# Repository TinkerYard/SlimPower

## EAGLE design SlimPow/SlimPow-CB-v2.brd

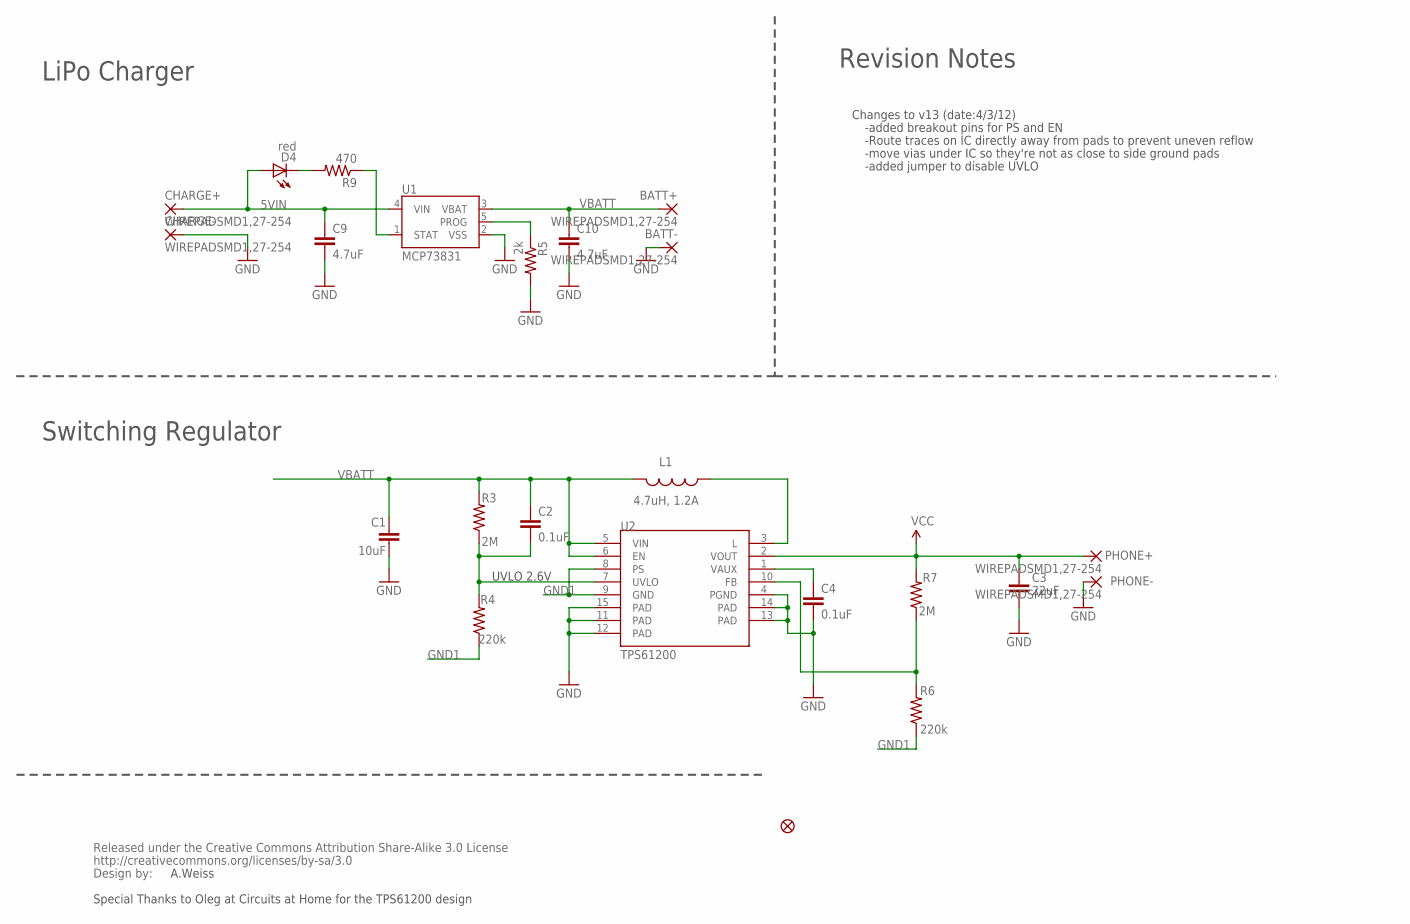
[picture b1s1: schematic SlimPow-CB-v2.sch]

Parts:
BATT+: WIREPADSMD1,27-254; SMD1,27-2,54
BATT-: WIREPADSMD1,27-254; SMD1,27-2,54
C1: 10uF; 1206
C2, C4: 0.1uF; 0402-CAP
C3: 22uF; 0805
C9, C10: 4.7uF; 0402-CAP
CHARGE+: WIREPADSMD1,27-254; SMD1,27-2,54
CHARGE-: WIREPADSMD1,27-254; SMD1,27-2,54
D4: red; LED-0603
JP15: FIDUCIALUFIDUCIAL; MICRO-FIDUCIAL
L1: 4.7uH, 1.2A; CDRH2D09
PHONE+: WIREPADSMD1,27-254; SMD1,27-2,54
PHONE-: WIREPADSMD1,27-254; SMD1,27-2,54
R3, R7: 2M; 0402-RES
R4, R6: 220k; 0402-RES
R5: 2k; 0402-RES
R9: 470; 0402-RES
U1: MCP73831; SOT23-5
U2: TPS61200; QFN-10_PAD
U$2: CREATIVE_COMMONS

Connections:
5VIN: C9.1, CHARGE+.1, D4.A, U1.4 (VIN)
FB: R6.2, R7.1, U2.10 (FB)
GND: BATT-.1, C1.2, C3.2, C4.2, C9.2, C10.2, CHARGE-.1, PHONE-.1, R5.2, U1.2 (VSS), U2.4 (PGND), U2.11 (PAD), U2.12 (PAD), U2.13 (PAD), U2.14 (PAD), U2.15 (PAD)
GND1: R4.1, R6.1, U2.8 (PS), U2.9 (GND)
unnamed: C4.1, U2.1 (VAUX)
unnamed: L1.P$1 (1), U2.3 (L)
unnamed: D4.C, R9.2
unnamed: R5.1, U1.5 (PROG)
unnamed: R9.1, U1.1 (STAT)
UVLO: C2.2, R3.1, R4.2, U2.7 (UVLO)
VBATT: BATT+.1, C1.1, C2.1, C10.1, L1.P$2 (2), R3.2, U1.3 (VBAT), U2.5 (VIN), U2.6 (EN)
VCC: C3.1, PHONE+.1, R7.2, U2.2 (VOUT)

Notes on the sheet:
UVLO 2.6V
Changes to v13 (date:4/3/12)
-added breakout pins for PS and EN
-Route traces on IC directly away from pads to prevent uneven reflow
-move vias under IC so they're not as close to side ground pads
-added jumper to disable UVLO
A.Weiss
Special Thanks to Oleg at Circuits at Home for the TPS61200 design
LiPo Charger
Switching Regulator
Revision Notes

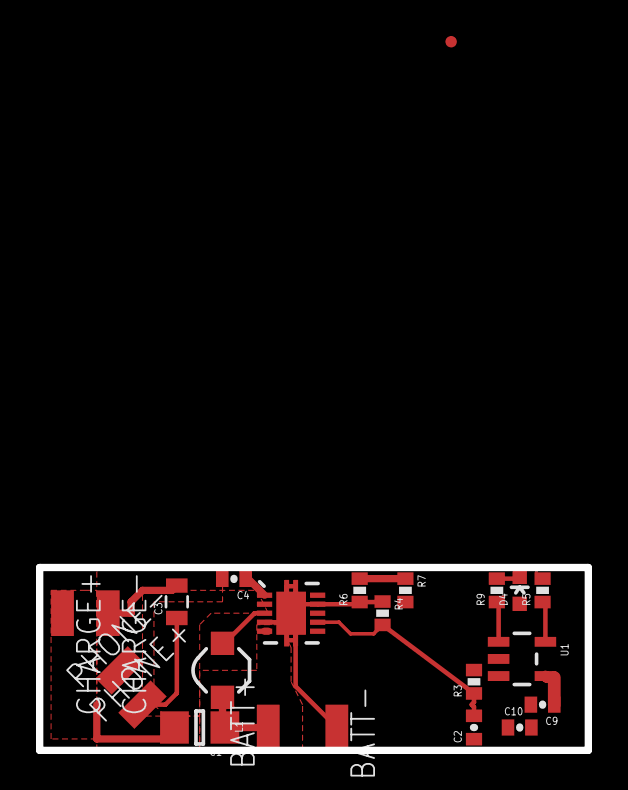
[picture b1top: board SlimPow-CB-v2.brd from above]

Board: 2 copper layers, 30.5 x 10.2 mm, 24 parts (0 on the bottom side), 12 nets.

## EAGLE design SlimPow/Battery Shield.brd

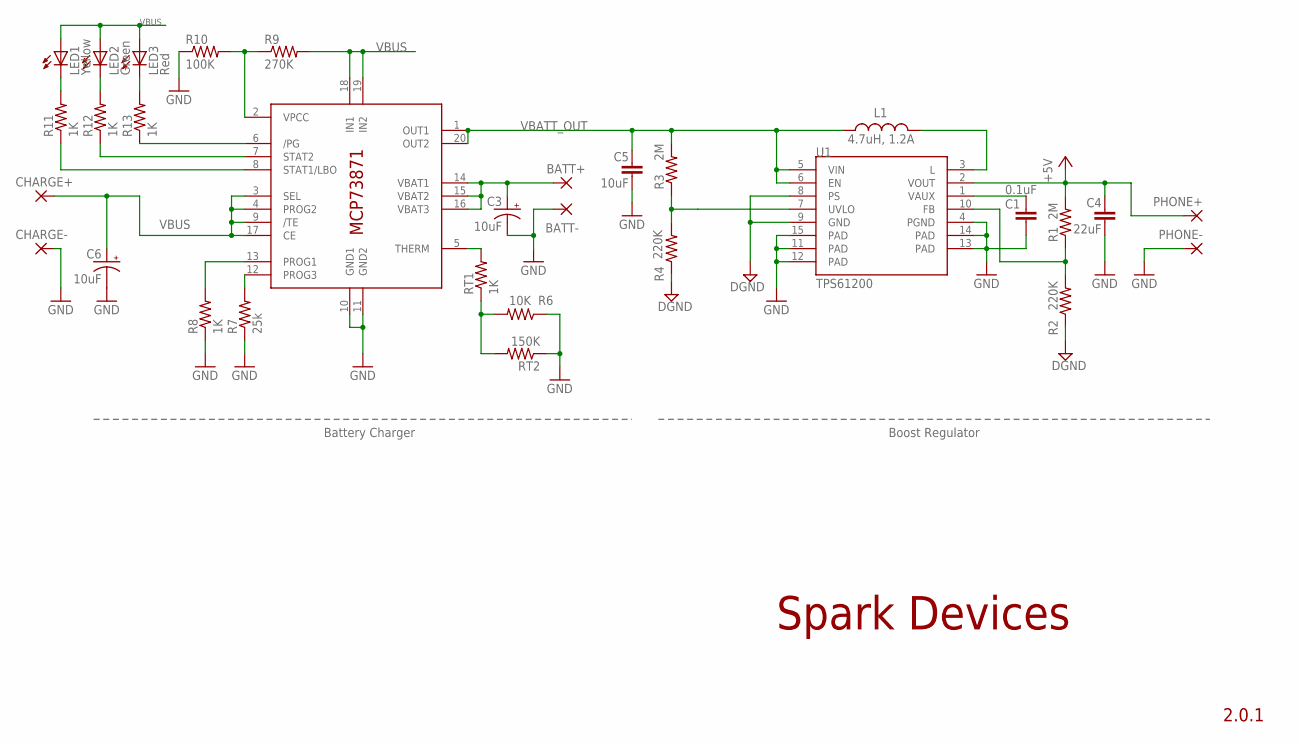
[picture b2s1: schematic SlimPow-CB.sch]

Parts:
BATT+: WIREPAD2,15/1,0; 2,15/1,0
BATT-: WIREPAD2,15/1,0; 2,15/1,0
C1: 0.1uF; 0402-CAP
C3, C6: 10uF; EIA3216
C4: 22uF; 0805
C5: 10uF; 1206
CHARGE+: WIREPAD2,15/1,0; 2,15/1,0
CHARGE-: WIREPAD2,15/1,0; 2,15/1,0
IC1: MCP73871; QFN20
L1: 4.7uH, 1.2A; CDRH2D09
LED1: Yellow; LED-0603
LED2: Green; LED-0603
LED3: Red; LED-0603
PHONE+: WIREPAD2,15/1,0; 2,15/1,0
PHONE-: WIREPAD2,15/1,0; 2,15/1,0
R1, R3: 2M; 0402-RES
R2, R4: 220K; 0402-RES
R6: 10K; 0402-RES
R7: 25k; 0402-RES
R8, R11, R12, R13: 1K; 0402-RES
R9: 270K; 0402-RES
R10: 100K; 0402-RES
RT1: 1K; 0402-RES
RT2: 150K; 0402-RES
U1: TPS61200; QFN-10_PAD

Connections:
+5V: C4.1, PHONE+.1, R1.2, U1.2 (VOUT)
DGND: R2.1, R4.1, U1.8 (PS), U1.9 (GND)
GND: BATT-.1, C1.2, C3.C (-), C4.2, C5.2, C6.C (-), CHARGE-.1, IC1.10 (GND1), IC1.11 (GND2), PHONE-.1, R6.1, R7.1, R8.1, R10.1, RT2.1, U1.4 (PGND), U1.11 (PAD), U1.12 (PAD), U1.13 (PAD), U1.14 (PAD), U1.15 (PAD)
unnamed: L1.P$2 (2), U1.3 (L)
unnamed: C1.1, U1.1 (VAUX)
unnamed: R3.1, R4.2, U1.7 (UVLO)
unnamed: R1.1, R2.2, U1.10 (FB)
unnamed: BATT+.1, C3.A (+), IC1.14 (VBAT1), IC1.15 (VBAT2), IC1.16 (VBAT3)
unnamed: IC1.8 (STAT1/LBO), R11.1
unnamed: R6.2, RT1.1, RT2.2
unnamed: LED1.C, R11.2
unnamed: IC1.5 (THERM), RT1.2
unnamed: LED2.C, R12.2
unnamed: IC1.12 (PROG3), R7.2
unnamed: IC1.2 (VPCC), R9.1, R10.2
unnamed: IC1.13 (PROG1), R8.2
unnamed: IC1.7 (STAT2), R12.1
unnamed: IC1.6 (/PG), R13.1
unnamed: LED3.C, R13.2
VBATT_OUT: C5.1, IC1.1 (OUT1), IC1.20 (OUT2), L1.P$1 (1), R3.2, U1.5 (VIN), U1.6 (EN)
VBUS: C6.A (+), CHARGE+.1, IC1.3 (SEL), IC1.4 (PROG2), IC1.9 (/TE), IC1.17 (CE), IC1.18 (IN1), IC1.19 (IN2), LED1.A, LED2.A, LED3.A, R9.2

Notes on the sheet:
Battery Charger
Boost Regulator
Spark Devices
2.0.1

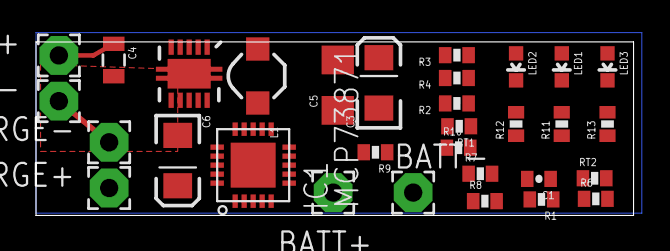
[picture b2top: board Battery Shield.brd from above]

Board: 2 copper layers, 33.2 x 9.6 mm, 31 parts (0 on the bottom side), 21 nets.

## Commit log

2014-02-18 Initialwork
2014-02-19 v1.1
2014-02-19 v1.2
2014-02-21 v2 using SparkFuns board

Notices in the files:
parts and their libraries:
SparkFun-PowerIC: Licensing: CC v3.0 Share-Alike You are welcome to use this library for commercial purposes.
SparkFun-Aesthetics: Released under the Creative Commons Attribution Share-Alike 3.0 License
SparkFun-Aesthetics: http://creativecommons.org/licenses/by-sa/3.0
